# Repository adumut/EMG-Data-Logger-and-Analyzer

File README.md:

=> Analog EMG data obtained from 4 channels are converted into digital data for Raspberry Pi Zero W with the ADS1115 module. 

=> Signals are analyzed in Raspbery Pi Zero WH via Python or MATLAB.

More details will be shared soon.

(The project is not finished yet.)

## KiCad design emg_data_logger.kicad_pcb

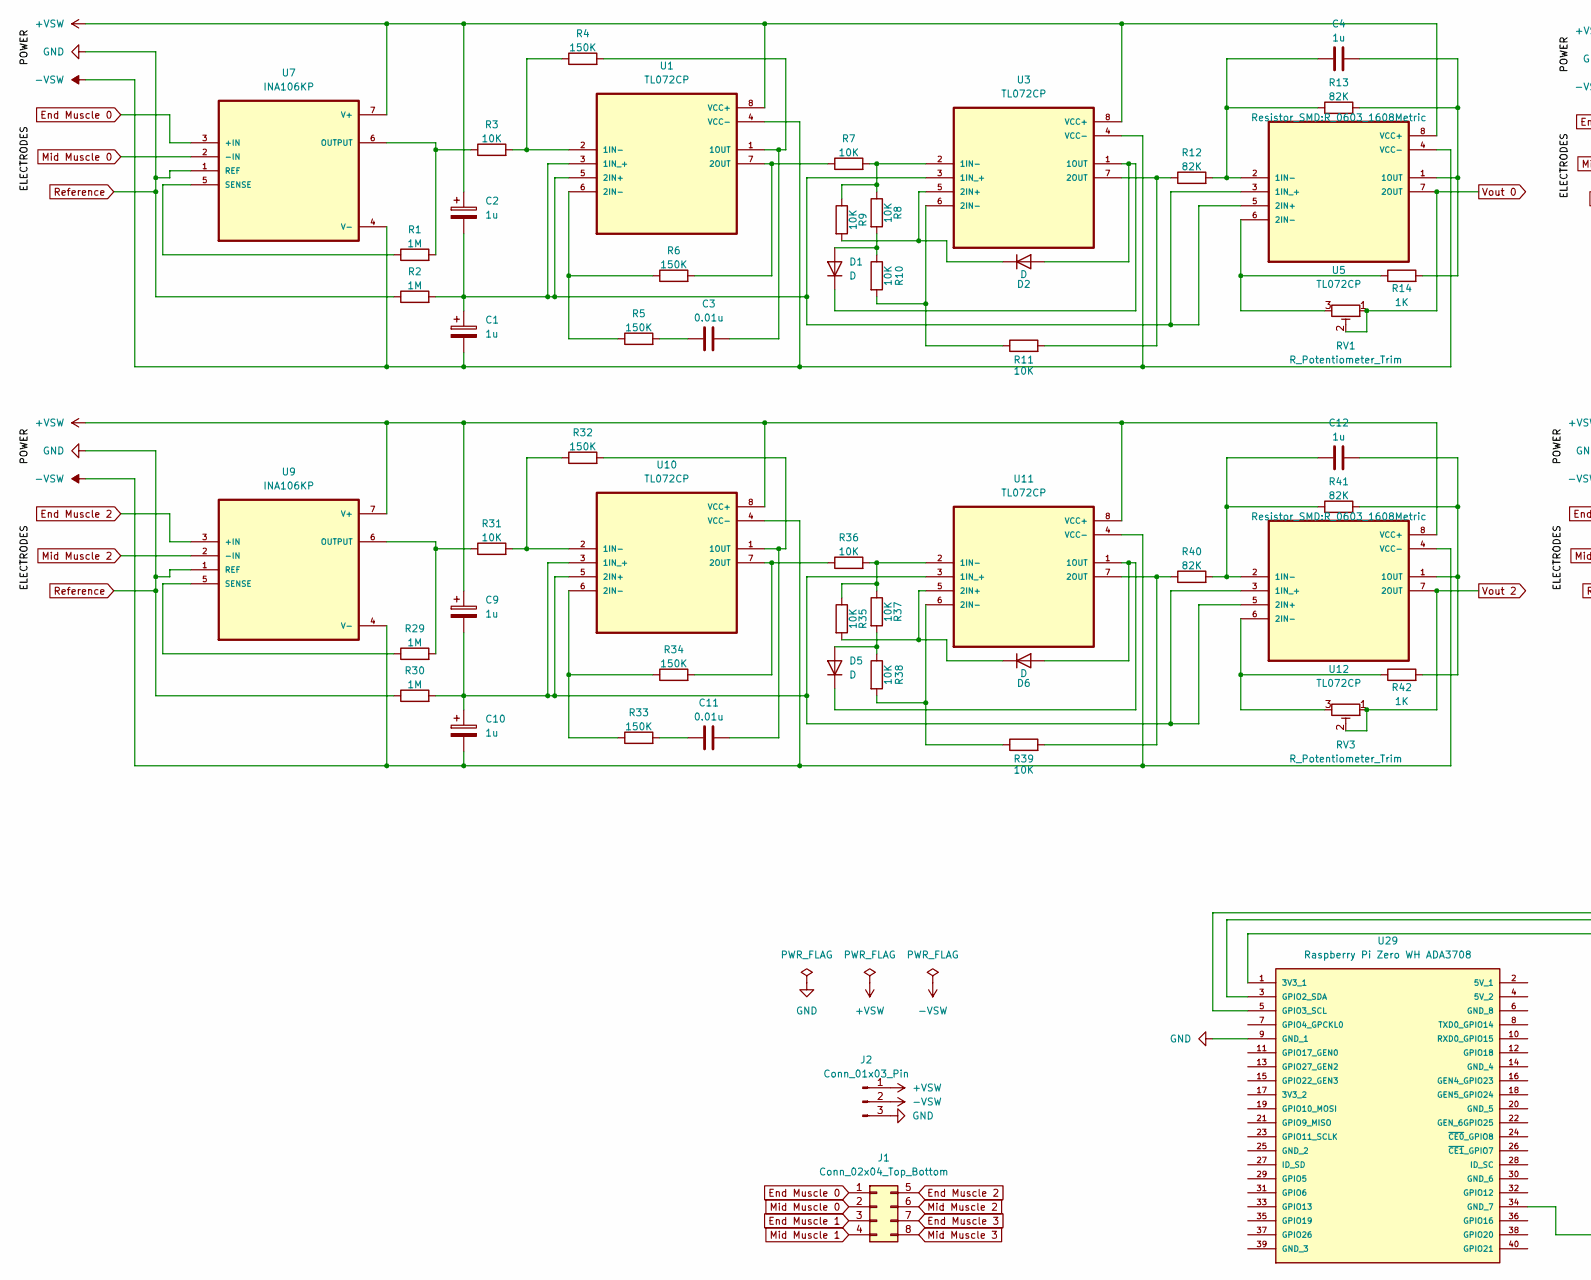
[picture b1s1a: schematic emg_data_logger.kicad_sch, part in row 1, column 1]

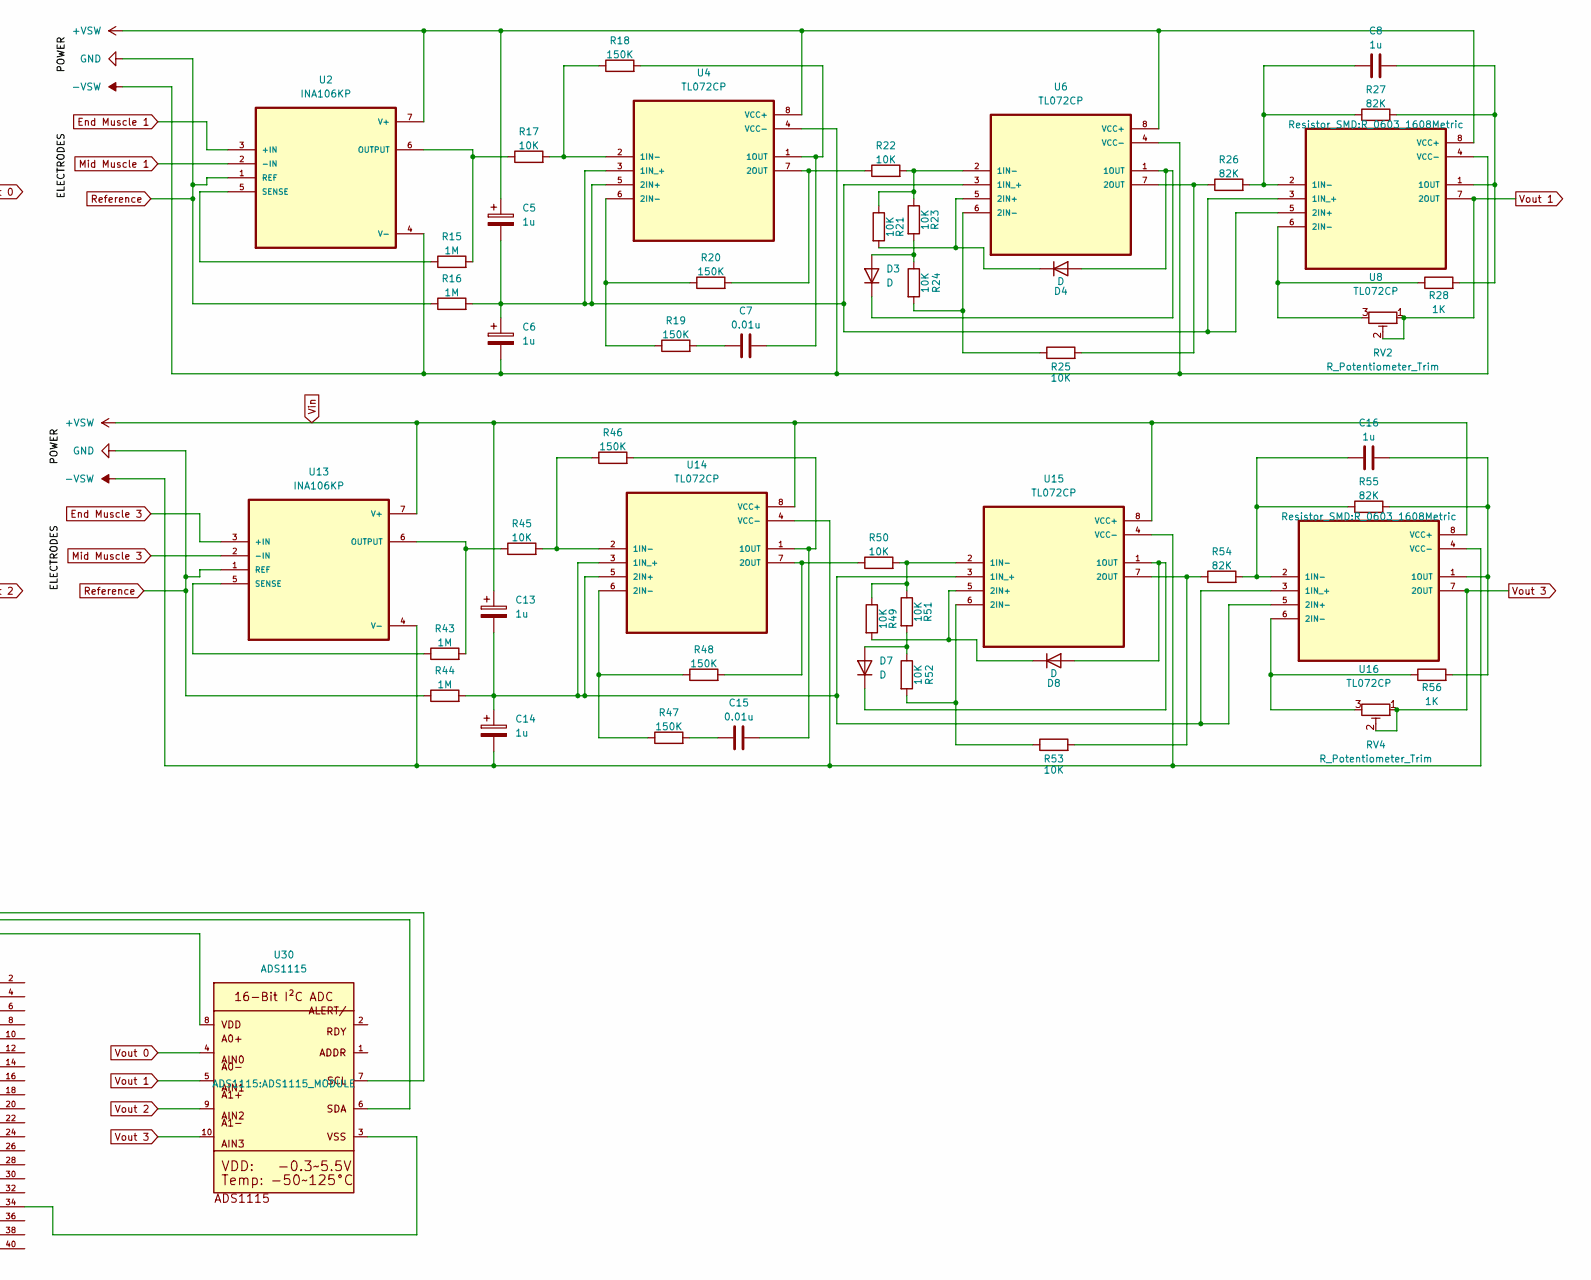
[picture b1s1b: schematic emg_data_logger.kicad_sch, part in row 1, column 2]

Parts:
C1, C2, C5, C6, C9, C10, C13, C14: 1u; CP_Radial_Tantal_D4.5mm_P5.00mm
C3, C7, C11, C15: 0.01u; C_Disc_D3.4mm_W2.1mm_P2.50mm
C4, C8, C12, C16: 1u; C_Disc_D3.4mm_W2.1mm_P2.50mm
D1, D2, D3, D4, D5, D6, D7, D8: D; D_0201_0603Metric
J1: Conn_02x04_Top_Bottom; Harwin_LTek-Male_2x04_P2.00mm_Vertical
J2: Conn_01x03_Pin; FanPinHeader_1x03_P2.54mm_Vertical
R1, R2, R15, R16, R29, R30, R43, R44: 1M; R_0603_1608Metric
R3, R7, R8, R9, R10, R11, R17, R21, R22, R23, R24, R25, R31, R35, R36, R37, R38, R39, R45, R49, R50, R51, R52, R53: 10K; R_0603_1608Metric
R4, R5, R6, R18, R19, R20, R32, R33, R34, R46, R47, R48: 150K; R_0603_1608Metric
R12, R13, R26, R27, R40, R41, R54, R55: 82K; R_0603_1608Metric
R14, R28, R42, R56: 1K; R_0603_1608Metric
RV1, RV2, RV3, RV4: R_Potentiometer_Trim; Potentiometer_Runtron_RM-063_Horizontal
U1, U3, U4, U5, U6, U8, U10, U11, U12, U14, U15, U16: TL072CP; DIP794W45P254L959H508Q8
U2, U7, U9, U13: INA106KP; DIP794W45P254L959H508Q8
U29: Raspberry Pi Zero WH ADA3708; MODULE_ADA3708
U30: ADS1115; ADS1115_MODULE

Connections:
-VSW: C1.2, C6.2, C10.2, C14.2, J2.2, U1.4 (VCC-), U2.4 (V-), U3.4 (VCC-), U4.4 (VCC-), U5.4 (VCC-), U6.4 (VCC-), U7.4 (V-), U8.4 (VCC-), U9.4 (V-), U10.4 (VCC-), U11.4 (VCC-), U12.4 (VCC-), U13.4 (V-), U14.4 (VCC-), U15.4 (VCC-), U16.4 (VCC-)
End Muscle 0: J1.1, U7.3 (+IN)
End Muscle 1: J1.3, U2.3 (+IN)
End Muscle 2: J1.5, U9.3 (+IN)
End Muscle 3: J1.7, U13.3 (+IN)
Mid Muscle 0: J1.2, U7.2 (-IN)
Mid Muscle 1: J1.4, U2.2 (-IN)
Mid Muscle 2: J1.6, U9.2 (-IN)
Mid Muscle 3: J1.8, U13.2 (-IN)
unnamed: C3.1, R5.2
unnamed: C7.1, R19.2
unnamed: C11.1, R33.2
unnamed: C15.1, R47.2
unnamed: D1.2 (A), R8.2, R10.1
unnamed: D1.1 (K), D2.2 (A), U3.1 (1OUT)
unnamed: D2.1 (K), R9.2, U3.5 (2IN+)
unnamed: D3.2 (A), R23.2, R24.1
unnamed: D3.1 (K), D4.2 (A), U6.1 (1OUT)
unnamed: D4.1 (K), R21.2, U6.5 (2IN+)
unnamed: D5.2 (A), R37.2, R38.1
unnamed: D5.1 (K), D6.2 (A), U11.1 (1OUT)
unnamed: D6.1 (K), R35.2, U11.5 (2IN+)
unnamed: D7.2 (A), R51.2, R52.1
unnamed: D7.1 (K), D8.2 (A), U15.1 (1OUT)
unnamed: D8.1 (K), R49.2, U15.5 (2IN+)
unnamed: R3.2, R4.1, U1.2 (1IN-)
unnamed: C1.1, C2.2, R2.2, U1.3 (1IN_+), U1.5 (2IN+), U3.3 (1IN_+), U5.3 (1IN_+), U5.5 (2IN+)
unnamed: C3.2, R4.2, U1.1 (1OUT)
unnamed: R5.1, R6.1, U1.6 (2IN-)
unnamed: R6.2, R7.1, U1.7 (2OUT)
unnamed: R15.2, R17.1, U2.6 (OUTPUT)
unnamed: R15.1, U2.5 (SENSE)
unnamed: R7.2, R8.1, R9.1, U3.2 (1IN-)
unnamed: R10.2, R11.1, U3.6 (2IN-)
unnamed: R11.2, R12.1, U3.7 (2OUT)
unnamed: R17.2, R18.1, U4.2 (1IN-)
unnamed: C5.2, C6.1, R16.2, U4.3 (1IN_+), U4.5 (2IN+), U6.3 (1IN_+), U8.3 (1IN_+), U8.5 (2IN+)
unnamed: C7.2, R18.2, U4.1 (1OUT)
unnamed: R19.1, R20.1, U4.6 (2IN-)
unnamed: R20.2, R22.1, U4.7 (2OUT)
unnamed: C4.1, R12.2, R13.1, U5.2 (1IN-)
unnamed: C4.2, R13.2, R14.2, U5.1 (1OUT)
unnamed: R14.1, RV1.3, U5.6 (2IN-)
unnamed: R21.1, R22.2, R23.1, U6.2 (1IN-)
unnamed: R24.2, R25.1, U6.6 (2IN-)
unnamed: R25.2, R26.1, U6.7 (2OUT)
unnamed: R1.2, R3.1, U7.6 (OUTPUT)
unnamed: R1.1, U7.5 (SENSE)
unnamed: C8.1, R26.2, R27.1, U8.2 (1IN-)
unnamed: C8.2, R27.2, R28.2, U8.1 (1OUT)
unnamed: R28.1, RV2.3, U8.6 (2IN-)
unnamed: R29.2, R31.1, U9.6 (OUTPUT)
unnamed: R29.1, U9.5 (SENSE)
unnamed: R31.2, R32.1, U10.2 (1IN-)
unnamed: C9.2, C10.1, R30.2, U10.3 (1IN_+), U10.5 (2IN+), U11.3 (1IN_+), U12.3 (1IN_+), U12.5 (2IN+)
unnamed: C11.2, R32.2, U10.1 (1OUT)
unnamed: R33.1, R34.1, U10.6 (2IN-)
unnamed: R34.2, R36.1, U10.7 (2OUT)
unnamed: R35.1, R36.2, R37.1, U11.2 (1IN-)
unnamed: R38.2, R39.1, U11.6 (2IN-)
unnamed: R39.2, R40.1, U11.7 (2OUT)
unnamed: C12.1, R40.2, R41.1, U12.2 (1IN-)
unnamed: C12.2, R41.2, R42.2, U12.1 (1OUT)
unnamed: R42.1, RV3.3, U12.6 (2IN-)
unnamed: R43.2, R45.1, U13.6 (OUTPUT)
unnamed: R43.1, U13.5 (SENSE)
unnamed: R45.2, R46.1, U14.2 (1IN-)
unnamed: C13.2, C14.1, R44.2, U14.3 (1IN_+), U14.5 (2IN+), U15.3 (1IN_+), U16.3 (1IN_+), U16.5 (2IN+)
unnamed: C15.2, R46.2, U14.1 (1OUT)
unnamed: R47.1, R48.1, U14.6 (2IN-)
unnamed: R48.2, R50.1, U14.7 (2OUT)
unnamed: R49.1, R50.2, R51.1, U15.2 (1IN-)
unnamed: R52.2, R53.1, U15.6 (2IN-)
unnamed: R53.2, R54.1, U15.7 (2OUT)
unnamed: C16.1, R54.2, R55.1, U16.2 (1IN-)
unnamed: C16.2, R55.2, R56.2, U16.1 (1OUT)
unnamed: R56.1, RV4.3, U16.6 (2IN-)
unnamed: U29.1 (3V3_1), U30.8
unnamed: U29.34 (GND_7), U30.3
unnamed: U29.3 (GPIO2_SDA), U30.6
unnamed: U29.5 (GPIO3_SCL), U30.7
Reference: J2.3, R2.1, R16.1, R30.1, R44.1, U2.1 (REF), U7.1 (REF), U9.1 (REF), U13.1 (REF), U29.9 (GND_1)
Vin: C2.1, C5.1, C9.1, C13.1, J2.1, U1.8 (VCC+), U2.7 (V+), U3.8 (VCC+), U4.8 (VCC+), U5.8 (VCC+), U6.8 (VCC+), U7.7 (V+), U8.8 (VCC+), U9.7 (V+), U10.8 (VCC+), U11.8 (VCC+), U12.8 (VCC+), U13.7 (V+), U14.8 (VCC+), U15.8 (VCC+), U16.8 (VCC+)
Vout 0: RV1.1, RV1.2, U5.7 (2OUT), U30.4
Vout 1: RV2.1, RV2.2, U8.7 (2OUT), U30.5
Vout 2: RV3.1, RV3.2, U12.7 (2OUT), U30.9
Vout 3: RV4.1, RV4.2, U16.7 (2OUT), U30.10

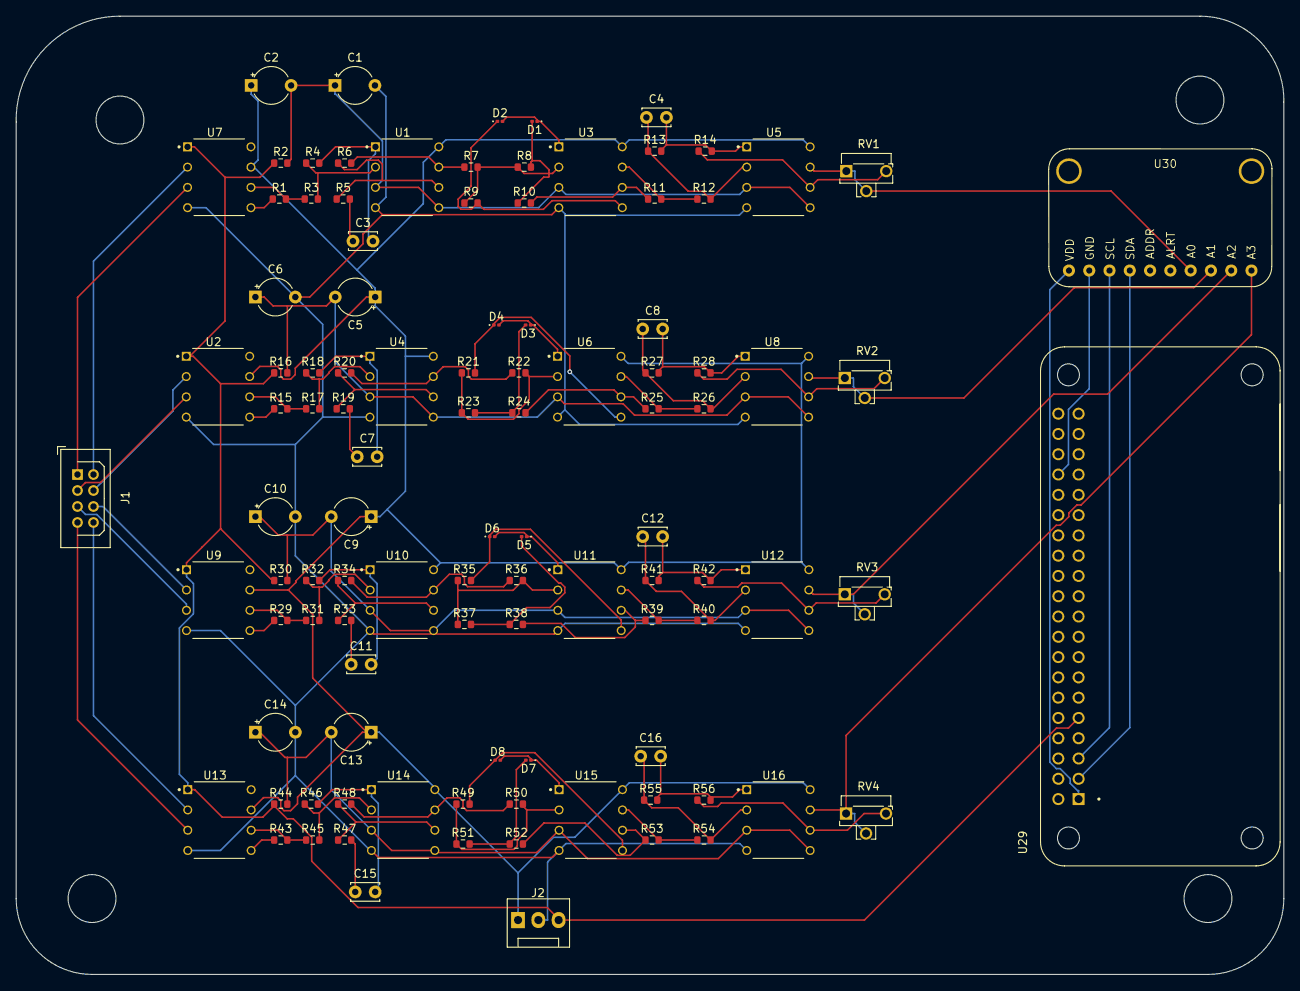
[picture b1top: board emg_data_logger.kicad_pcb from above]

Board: 2 copper layers, 158.8 x 120.0 mm, 104 parts (0 on the bottom side), 87 nets.
